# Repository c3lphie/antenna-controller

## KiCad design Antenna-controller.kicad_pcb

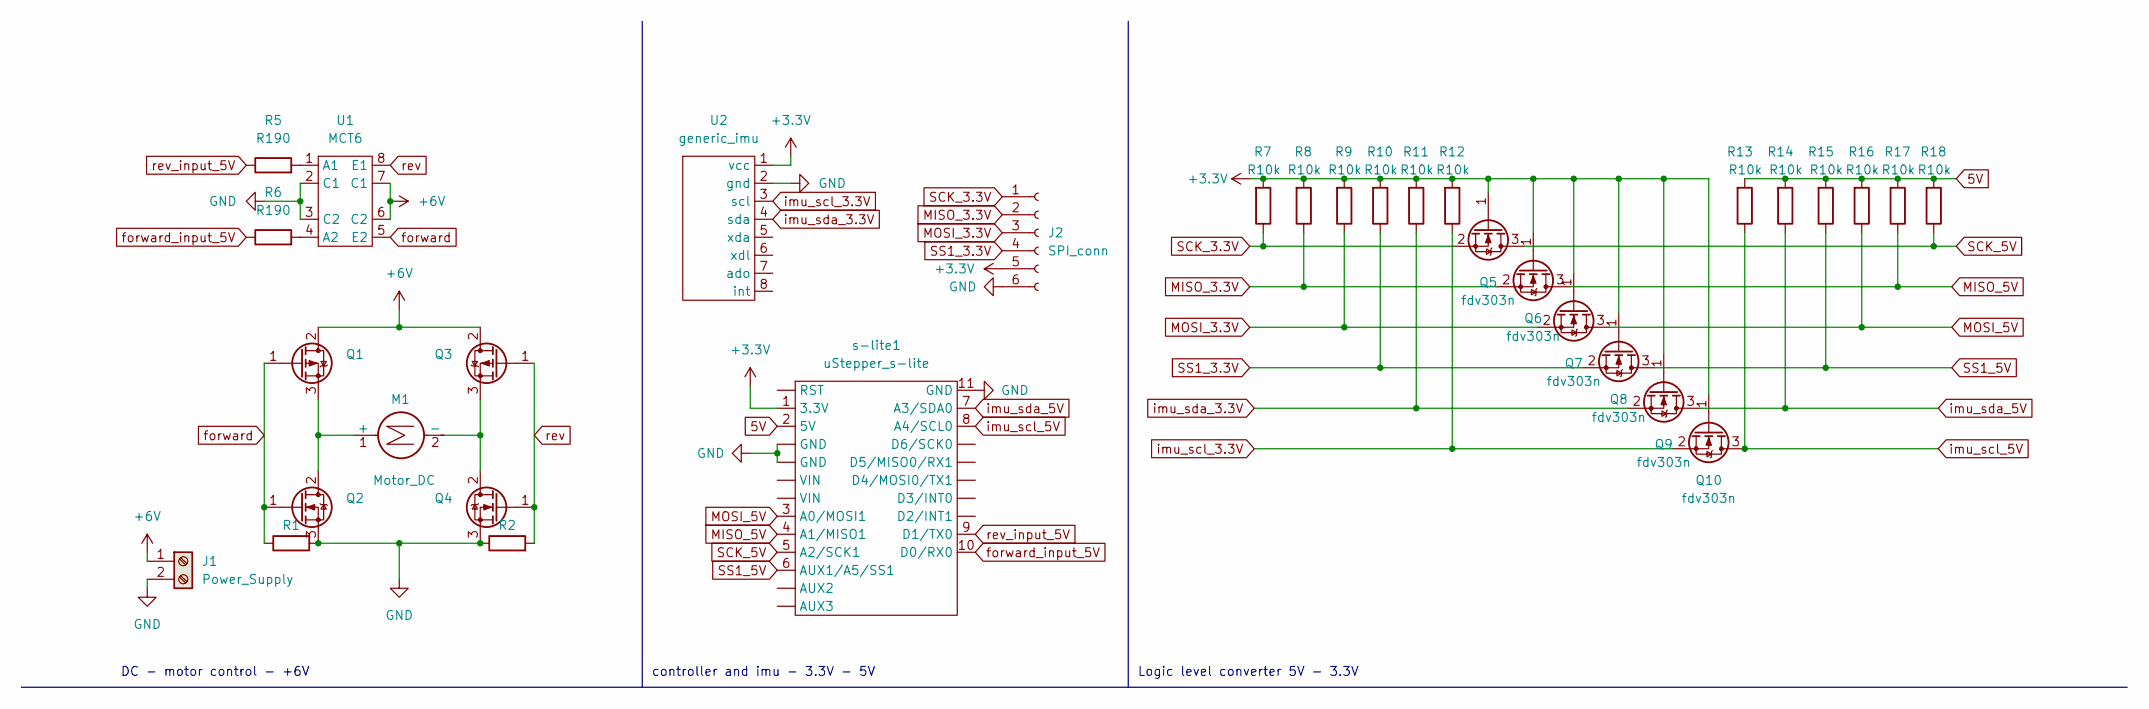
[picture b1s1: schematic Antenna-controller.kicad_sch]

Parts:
J1: Power_Supply; TerminalBlock_Altech_AK300-2_P5.00mm
J2: SPI_conn; PinHeader_1x06_P2.54mm_Horizontal
M1: Motor_DC; TerminalBlock_Altech_AK300-2_P5.00mm
Q1, Q2, Q3, Q4: (no value)
Q5, Q6, Q7, Q8, Q9, Q10: fdv303n; SOT-23_Handsoldering
R1, R2: (no value)
R5, R6: R190; R_Axial_DIN0207_L6.3mm_D2.5mm_P10.16mm_Horizontal
R7, R8, R9, R10, R11, R12, R13, R14, R15, R16, R17, R18: R10k; R_Axial_DIN0207_L6.3mm_D2.5mm_P10.16mm_Horizontal
U1: MCT6; DIP-8_W10.16mm_LongPads
U2: generic_imu; PinHeader_1x08_P2.54mm_Horizontal
s-lite1: uStepper_s-lite; PinHeader_1x11_P2.54mm_Horizontal

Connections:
5V: R13.2, R14.2, R15.2, R16.2, R17.2, R18.2, s-lite1.2 (5V)
+3V3: J2.5, Q5.1 (G), Q6.1 (G), Q7.1 (G), Q8.1 (G), Q9.1 (G), Q10.1 (G), R7.2, R8.2, R9.2, R10.2, R11.2, R12.2, U2.1 (vcc), s-lite1.1 (3.3V)
+6V: J1.1, Q1.2 (D), Q3.2 (D), U1.6 (C2), U1.7 (C1)
GND: J1.2, J2.6, Q2.3 (S), Q4.3 (S), R1.2, R2.1, U1.2 (C1), U1.3 (C2), U2.2 (gnd), s-lite1. (AUX2), s-lite1.11 (GND)
MISO_3.3V: J2.2, Q6.2 (S), R8.1
MISO_5V: Q6.3 (D), R17.1, s-lite1.4 (A1/MISO1)
MOSI_3.3V: J2.3, Q7.2 (S), R9.1
MOSI_5V: Q7.3 (D), R16.1, s-lite1.3 (A0/MOSI1)
unnamed: M1.1 (+), Q1.3 (S), Q2.2 (D)
unnamed: M1.2 (-), Q3.3 (S), Q4.2 (D)
unnamed: R5.2, U1.1 (A1)
unnamed: R6.2, U1.4 (A2)
SCK_3.3V: J2.1, Q5.2 (S), R7.1
SCK_5V: Q5.3 (D), R18.1, s-lite1.5 (A2/SCK1)
SS1_3.3V: J2.4, Q8.2 (S), R10.1
SS1_5V: Q8.3 (D), R15.1, s-lite1.6 (AUX1/A5/SS1)
forward: Q1.1 (G), Q2.1 (G), R1.1, U1.5 (E2)
forward_input_5V: R6.1, s-lite1.10 (D0/RX0)
imu_scl_3.3V: Q10.2 (S), R12.1, U2.3 (scl)
imu_scl_5V: Q10.3 (D), R13.1, s-lite1.8 (A4/SCL0)
imu_sda_3.3V: Q9.2 (S), R11.1, U2.4 (sda)
imu_sda_5V: Q9.3 (D), R14.1, s-lite1.7 (A3/SDA0)
rev: Q3.1 (G), Q4.1 (G), R2.2, U1.8 (E1)
rev_input_5V: R5.1, s-lite1.9 (D1/TX0)

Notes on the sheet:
DC - motor control - +6V
Logic level converter 5V - 3.3V
controller and imu - 3.3V - 5V

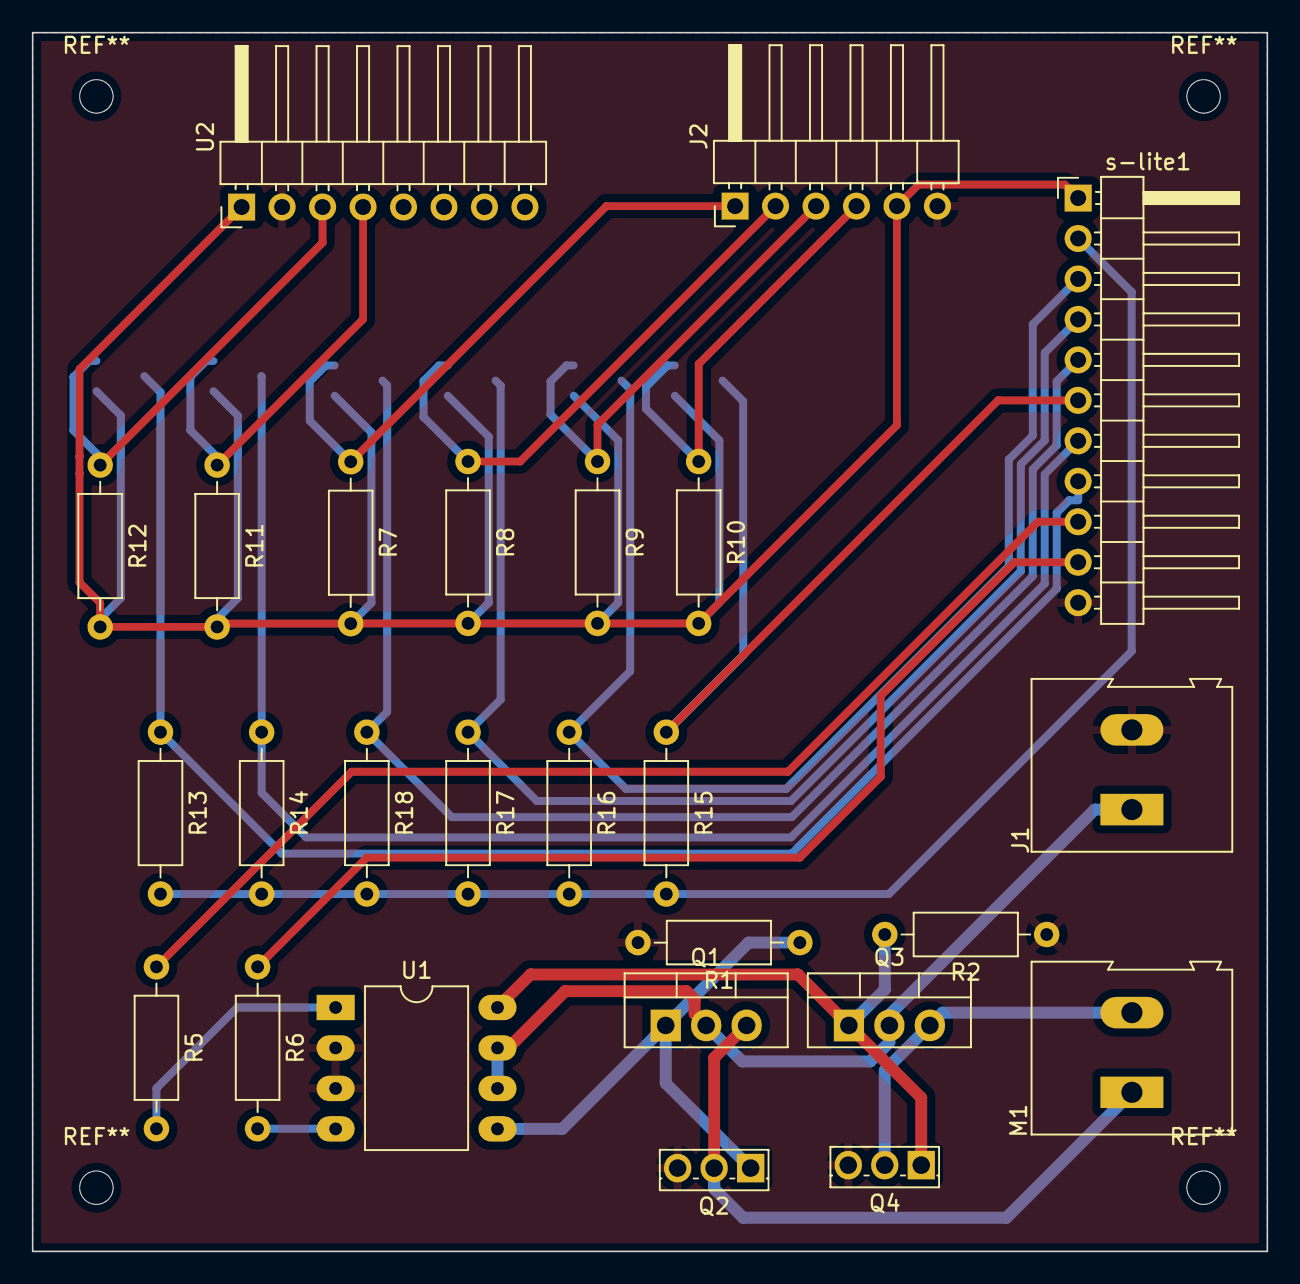
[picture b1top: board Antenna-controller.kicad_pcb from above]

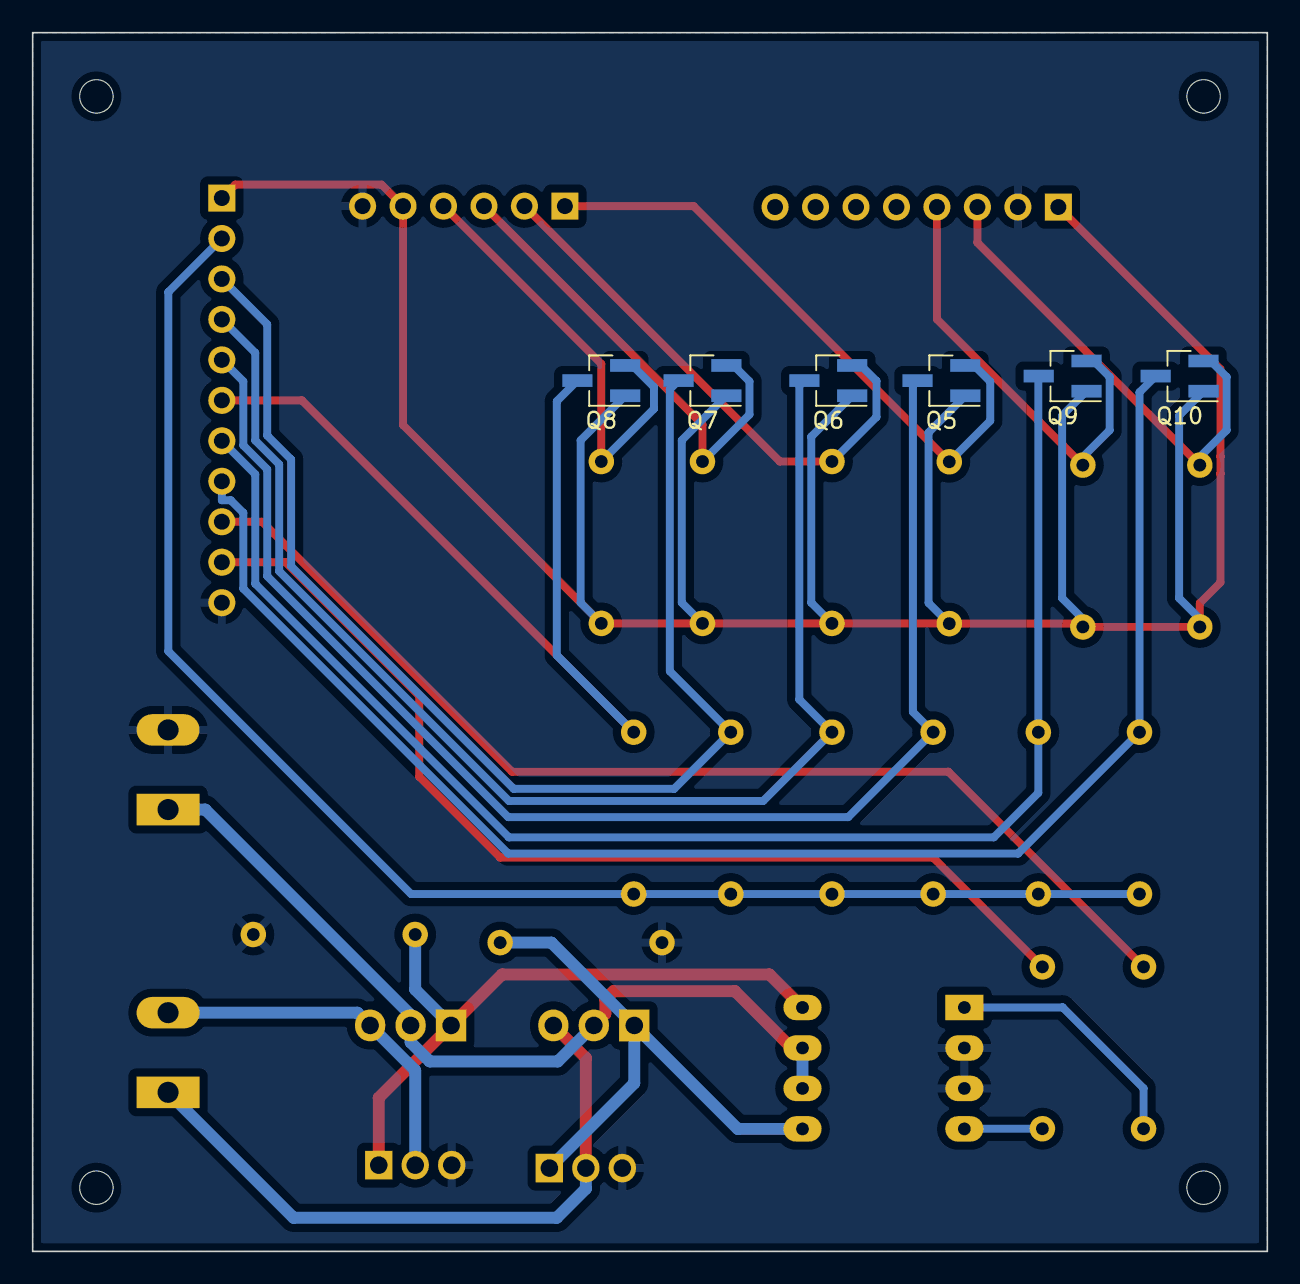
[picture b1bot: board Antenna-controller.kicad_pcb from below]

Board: 2 copper layers, 77.5 x 76.5 mm, 32 parts (6 on the bottom side), 24 nets.

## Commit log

2022-03-18 Initial commit
    Basically done with PCB and schematics.
    Started working on the code
2022-04-18 idk doing a backup
2022-05-03 Added Pinout diagram
2022-05-03 Update of PCB
2022-05-10 Added 2. revision of schematic
